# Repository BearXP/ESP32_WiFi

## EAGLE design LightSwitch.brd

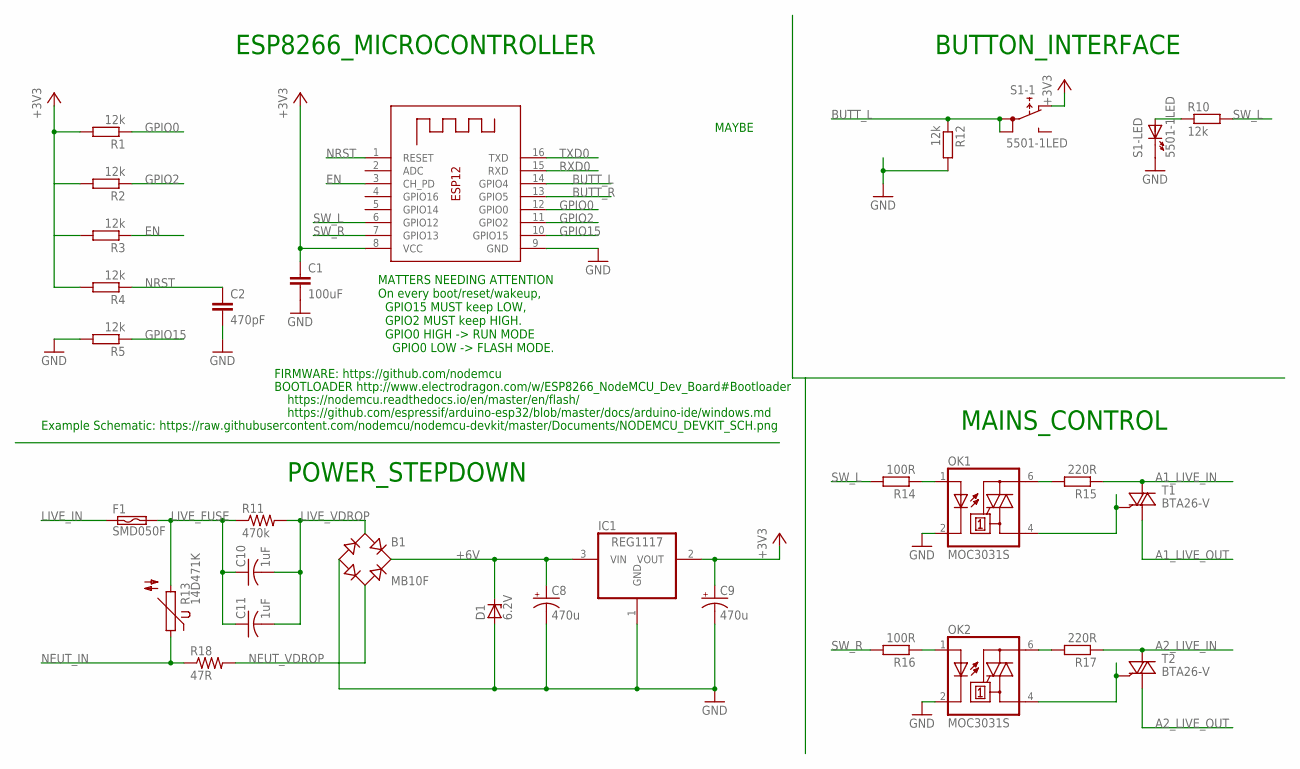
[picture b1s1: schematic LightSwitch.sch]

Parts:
B1: MB10F; SOIC-4
C1: 100uF; C0805K
C2: 470pF; C0805K
C8, C9: 470u; E3,5-8
C10, C11: 1uF; C225-074X268
D1: 6.2V; SMB
F1: SMD050F
IC1: REG1117; SOT223
OK1, OK2: MOC3031S; DIL6-SMD
R1, R2, R3, R4, R5, R10, R12: 12k; M0805
R11: 470k; 0309/12
R13: 14D471K; S07K40
R14, R16: 100R; M0805
R15, R17: 220R; M0805
R18: 47R; 0309/12
S1: 5501-1LED
T1, T2: BTA26-V; TOP3S-1
X1: ESP-12

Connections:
+3V1: R2.2
+3V2: R3.2
+3V3: C1.1, C9.+, IC1.2 (VOUT), R1.2, R4.2, S1.NC, X1.8 (VCC)
+6V: B1.+, C8.+, D1.C, IC1.3 (VIN)
A1_LIVE_IN: R15.1, T1.A2
A1_LIVE_OUT: T1.A1
A2_LIVE_IN: R17.1, T2.A2
A2_LIVE_OUT: T2.A1
BUTT_L: R12.1, S1.1A, S1.1B, X1.14 (GPIO4)
BUTT_R: X1.13 (GPIO5)
EN: R3.1, X1.3 (CH_PD)
GND: B1.-, C1.2, C2.2, C8.-, C9.-, D1.A, IC1.1 (GND), OK1.2 (C), OK2.2 (C), R5.2, R12.2, S1.- (K), X1.9 (GND)
GPIO0: R1.1, X1.12 (GPIO0)
GPIO2: R2.1, X1.11 (GPIO2)
GPIO15: R5.1, X1.10 (GPIO15)
LIVE_FUSE: C10.1, C11.1, F1.2, R11.1, R13.2
LIVE_IN: F1.1
LIVE_VDROP: B1.~1 (AC1), C10.2, C11.2, R11.2
unnamed: R10.1, S1.+ (A)
unnamed: OK1.1 (A), R14.1
unnamed: OK1.6 (A2), R15.2
unnamed: OK1.4 (A1), T1.G
unnamed: OK2.1 (A), R16.1
unnamed: OK2.6 (A2), R17.2
unnamed: OK2.4 (A1), T2.G
NEUT_IN: R13.1, R18.1
NEUT_VDROP: B1.~2 (AC2), R18.2
NRST: C2.1, R4.1, X1.1 (RESET)
RXD0: X1.15 (RXD)
SW_L: R10.2, R14.2, X1.6 (GPIO12)
SW_R: R16.2, X1.7 (GPIO13)
TXD0: X1.16 (TXD)

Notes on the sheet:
MATTERS NEEDING ATTENTION On every boot/reset/wakeup, GPIO15 MUST keep LOW, GPIO2 MUST keep HIGH. GPIO0 HIGH -> RUN MODE GPIO0 LOW -> FLASH MODE.
MAYBE
FIRMWARE: https://github.com/nodemcu
Example Schematic: https://raw.githubusercontent.com/nodemcu/nodemcu-devkit/master/Documents/NODEMCU_DEVKIT_SCH.png
BOOTLOADER http://www.electrodragon.com/w/ESP8266_NodeMCU_Dev_Board#Bootloader
https://nodemcu.readthedocs.io/en/master/en/flash/
https://github.com/espressif/arduino-esp32/blob/master/docs/arduino-ide/windows.md
MAINS_CONTROL
BUTTON_INTERFACE
ESP8266_MICROCONTROLLER
POWER_STEPDOWN

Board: 2 copper layers, 30 parts (0 on the bottom side), 24 nets, no tracks yet.

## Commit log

2017-08-27 Start
2017-09-03 working
2017-09-10 Light switch arrangement. Removed programmer.
2017-09-10 Added Google Home Assistant details
